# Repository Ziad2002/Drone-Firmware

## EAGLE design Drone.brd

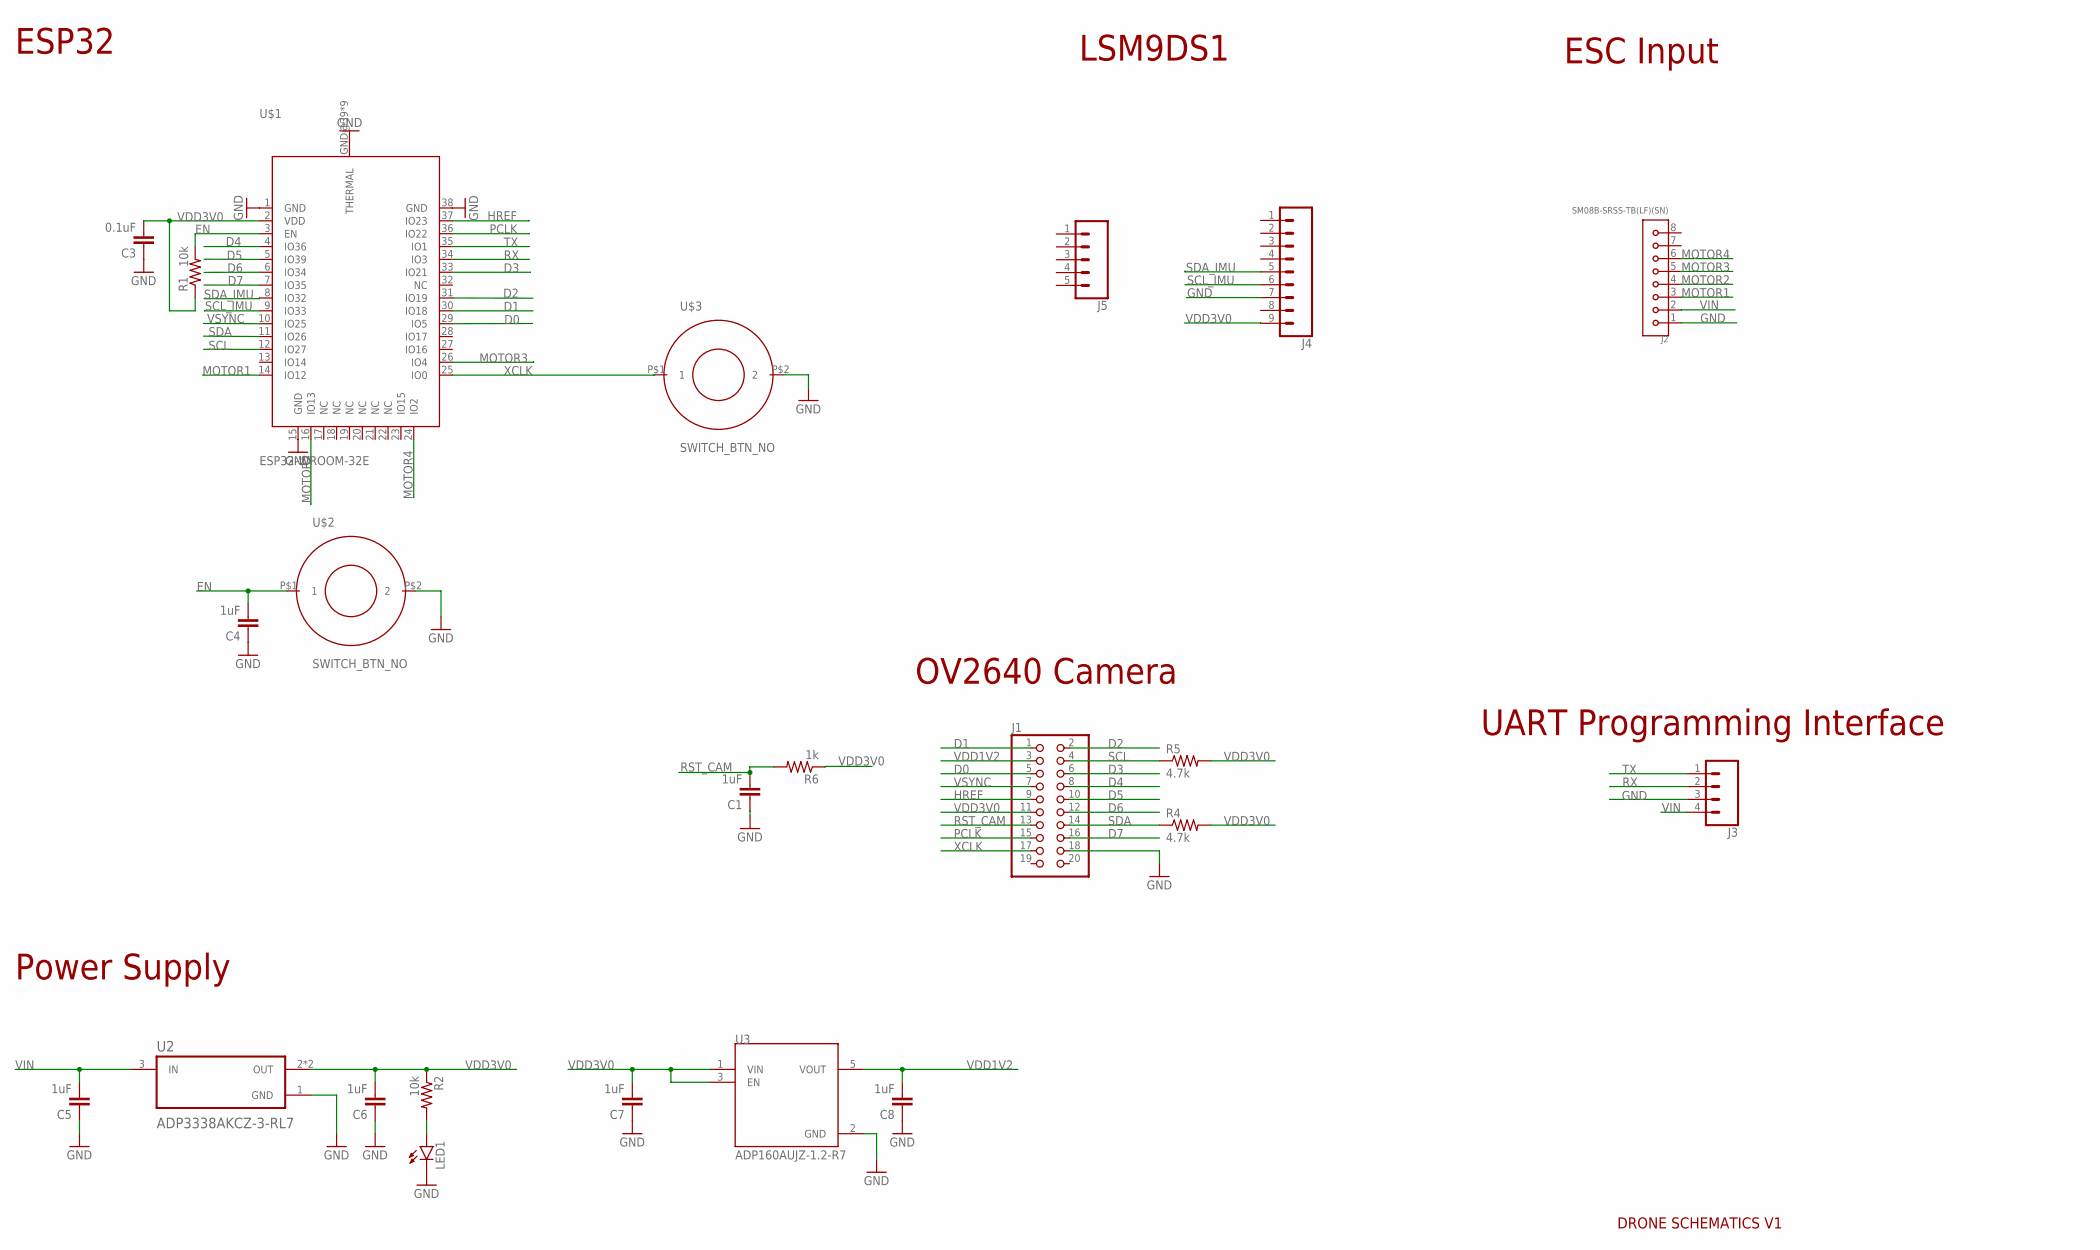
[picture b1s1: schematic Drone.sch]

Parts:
C1, C4, C5, C6, C7, C8: 1uF; 0805
C3: 0.1uF; 0805
J1: PINHD-2X10; 2X10
J2: SM08B-SRSS-TB(LF)(SN); JST_SM08B-SRSS-TB(LF)(SN)
J3: CONN_04PTH; 1X04
J4: CONN_09NO_SILK; 1X09_NO_SILK
J5: CONN_05NO_SILK; 1X05_NO_SILK
LED1: LED0603; LED-0603
R1, R2: 10k; 0805
R4, R5: 4.7k; 0805
R6: 1k; 0805
U2: ADP3338AKCZ-3-RL7; SOT230P700X180-4N
U3: ADP160AUJZ-1.2-R7; SOT95P280X100-5N
U$1: ESP32-WROOM-32E
U$2, U$3: SWITCH_BTN_NO; BTN_2

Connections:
D0: J1.5, U$1.29 (IO5)
D1: J1.1, U$1.30 (IO18)
D2: J1.2, U$1.31 (IO19)
D3: J1.6, U$1.33 (IO21)
D4: J1.8, U$1.4 (IO36)
D5: J1.10, U$1.5 (IO39)
D6: J1.12, U$1.6 (IO34)
D7: J1.16, U$1.7 (IO35)
EN: C4.2, R1.2, U$1.3 (EN), U$2.P$1 (1)
GND: C1.1, C3.1, C4.1, C5.1, C6.1, C7.1, C8.1, J1.18, J2.1, J3.3, J4.7, LED1.C, U2.1 (GND), U3.2 (GND), U$1.1 (GND), U$1.15 (GND), U$1.38 (GND), U$1.GND@39 (THERMAL), U$1.GND@40 (THERMAL), U$1.GND@41 (THERMAL), U$1.GND@42 (THERMAL), U$1.GND@43 (THERMAL), U$1.GND@44 (THERMAL), U$1.GND@45 (THERMAL), U$1.GND@46 (THERMAL), U$1.GND@47 (THERMAL), U$2.P$2 (2), U$3.P$2 (2)
HREF: J1.9, U$1.37 (IO23)
MOTOR1: J2.3, U$1.14 (IO12)
MOTOR2: J2.4, U$1.16 (IO13)
MOTOR3: J2.5, U$1.26 (IO4)
MOTOR4: J2.6, U$1.24 (IO2)
unnamed: LED1.A, R2.2
PCLK: J1.15, U$1.36 (IO22)
RST_CAM: C1.2, J1.13, R6.2
RX: J3.2, U$1.34 (IO3)
SCL: J1.4, R5.1, U$1.12 (IO27)
SCL_IMU: J4.6, U$1.9 (IO33)
SDA: J1.14, R4.1, U$1.11 (IO26)
SDA_IMU: J4.5, U$1.8 (IO32)
TX: J3.1, U$1.35 (IO1)
VDD1V2: C8.2, J1.3, U3.5 (VOUT)
VDD3V0: C3.2, C6.2, C7.2, J1.11, J4.9, R1.1, R2.1, R4.2, R5.2, R6.1, U2.2 (OUT), U2.4 (OUT), U3.1 (VIN), U3.3 (EN), U$1.2 (VDD)
VIN: C5.2, J2.2, J3.4, U2.3 (IN)
VSYNC: J1.7, U$1.10 (IO25)
XCLK: J1.17, U$1.25 (IO0), U$3.P$1 (1)

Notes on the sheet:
Power Supply
ESP32
LSM9DS1
OV2640 Camera
UART Programming Interface
ESC Input
DRONE SCHEMATICS V1

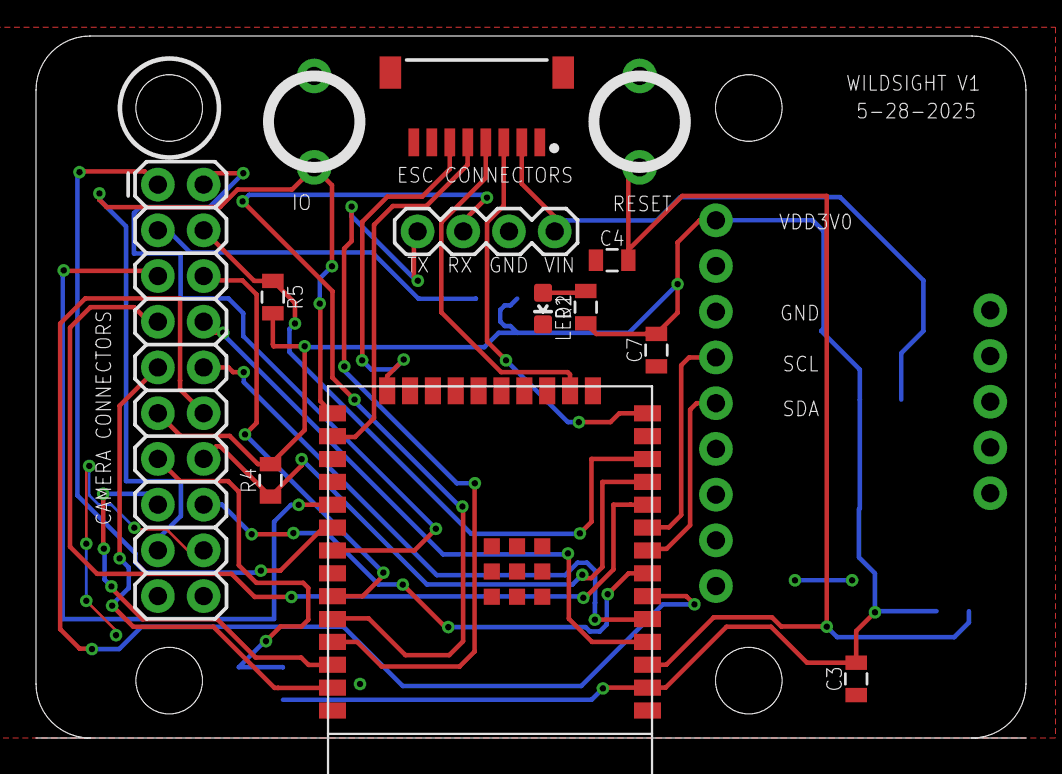
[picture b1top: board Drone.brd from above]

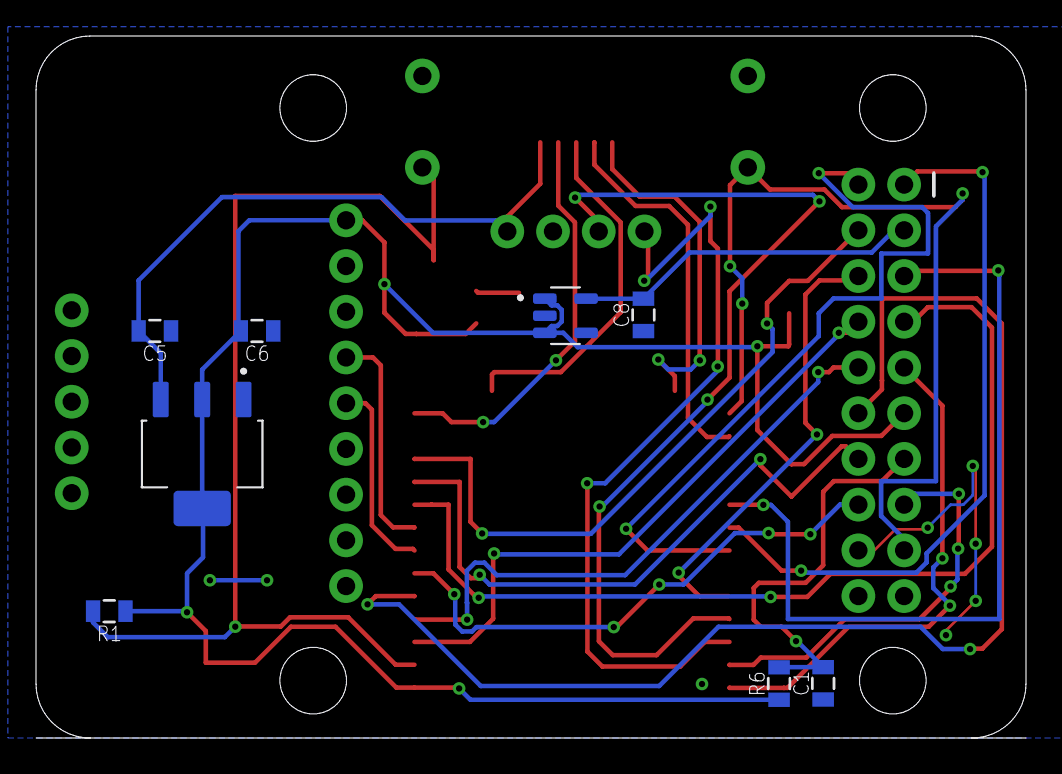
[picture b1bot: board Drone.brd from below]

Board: 2 copper layers, 55.0 x 39.0 mm, 23 parts (8 on the bottom side), 29 nets.

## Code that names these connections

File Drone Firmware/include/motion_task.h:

#ifndef MOTION_TASK_H
#define MOTION_TASK_H

void initMotionTask();

#define MOTOR1_PIN 12
#define MOTOR2_PIN 13
#define MOTOR3_PIN 4
#define MOTOR4_PIN 2

#define ESC1_CHANNEL 0
#define ESC2_CHANNEL 1
#define ESC3_CHANNEL 2
#define ESC4_CHANNEL 3
#define ESC_FREQ 50
#define ESC_RES_BITS 12

#endif

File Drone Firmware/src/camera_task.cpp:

#include "camera_task.h"
#include <Arduino.h>
#include <WiFi.h>
#include <WebSocketsClient.h>
#include "esp_camera.h"
#include "freertos/FreeRTOS.h"
#include "freertos/task.h"



const char* server_host = "18.223.203.35";
const uint16_t server_port = 8888;
const char* server_path = "/esp32_image";

WebSocketsClient webSocket;

void webSocketEvent(WStype_t type, uint8_t * payload, size_t length) {
  if (type == WStype_CONNECTED) {
    Serial.println("WebSocket connected");
  } else if (type == WStype_DISCONNECTED) {
    Serial.println("WebSocket disconnected");
  }
}

void sendFrame() {
  camera_fb_t *fb = esp_camera_fb_get();
  if (!fb) {
    Serial.println("Camera capture failed");
    return;
  }

  if (webSocket.isConnected()) {
    webSocket.sendBIN(fb->buf, fb->len);
    //Serial.printf("Sent %d bytes", fb->len);
  }

  esp_camera_fb_return(fb);
}

void cameraTask(void *pvParameters) {
  while (true) {
    webSocket.loop();
    if (webSocket.isConnected()) {
      sendFrame();
    }
    vTaskDelay(100 / portTICK_PERIOD_MS); // ~10 FPS
  }
}

void initCameraTask() {
  if (WiFi.status() != WL_CONNECTED) {
    Serial.println("WiFi not connected - Camera task will not start");
    return;
  }
  camera_config_t config;
  config.ledc_channel = LEDC_CHANNEL_0;
  config.ledc_timer = LEDC_TIMER_0;
  config.pin_d0 = Y2_GPIO_NUM;
  config.pin_d1 = Y3_GPIO_NUM;
  config.pin_d2 = Y4_GPIO_NUM;
  config.pin_d3 = Y5_GPIO_NUM;
  config.pin_d4 = Y6_GPIO_NUM;
  config.pin_d5 = Y7_GPIO_NUM;
  config.pin_d6 = Y8_GPIO_NUM;
  config.pin_d7 = Y9_GPIO_NUM;
  config.pin_xclk = XCLK_GPIO_NUM;
  config.pin_pclk = PCLK_GPIO_NUM;
  config.pin_vsync = VSYNC_GPIO_NUM;
  config.pin_href = HREF_GPIO_NUM;
  config.pin_sccb_sda = SIOD_GPIO_NUM;
  config.pin_sccb_scl = SIOC_GPIO_NUM;
  config.pin_pwdn = PWDN_GPIO_NUM;
  config.pin_reset = RESET_GPIO_NUM;
  config.xclk_freq_hz = 20000000;  // More stable than 20 MHz
  config.pixel_format = PIXFORMAT_JPEG;
  
  if (psramFound()) {
    config.frame_size = FRAMESIZE_VGA;
    config.jpeg_quality = 10;
    config.fb_count = 2;
  } else {
    config.frame_size = FRAMESIZE_CIF;
    config.jpeg_quality = 12;
    config.fb_count = 1;
  }

  config.fb_location = CAMERA_FB_IN_DRAM;

  esp_err_t err = esp_camera_init(&config);
  if (err != ESP_OK) {
    Serial.printf("❌ Camera init failed with error 0x%x\n", err);
  } else {
    Serial.println("✅ Camera initialized");
  }

  webSocket.begin(server_host, server_port, server_path);
  webSocket.onEvent(webSocketEvent);
  webSocket.setReconnectInterval(5000);

  xTaskCreatePinnedToCore(cameraTask, "CameraTask", 8192, NULL, 1, NULL, 1);
}

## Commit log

2025-04-22 Send commands from the server to the esp32
2025-04-28 add movements
2025-05-12 kalman filter
2025-06-06 updated firmware
2025-06-09 make starting button for the dorne

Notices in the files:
parts and their libraries:
SparkFun-Retired: Licensing: Creative Commons ShareAlike 4.0 International - https://creativecommons.org/licenses/by-sa/4.0
